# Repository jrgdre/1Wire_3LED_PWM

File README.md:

# 1Wire_3LED_PWM
How to drive 3 LEDs with 1 wire using Texas Intrument's TLC59731 PWM chip.

Find the in depth documentation at http://www.drechsler-it.de/Electronics_1Wire3LedPWM_TLC59731.html

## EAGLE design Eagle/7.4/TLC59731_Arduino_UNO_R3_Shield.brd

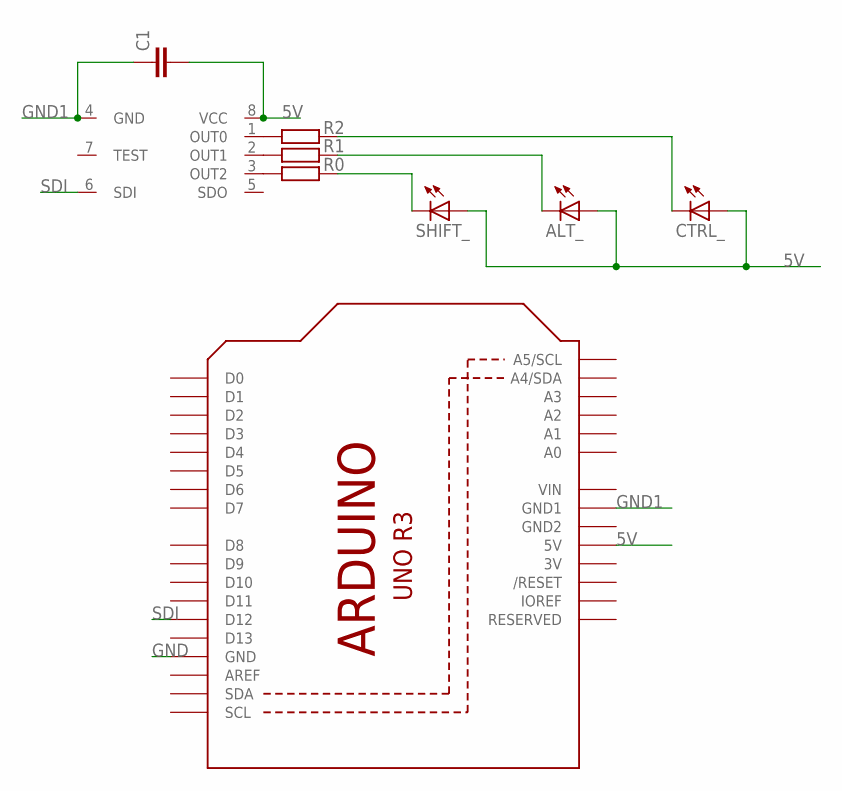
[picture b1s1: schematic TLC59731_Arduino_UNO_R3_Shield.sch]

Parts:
ALT_: LEDSMT1206; 1206
C1: CC0402; C0402
CTRL_: LEDSMT1206; 1206
M2: ARDUINO_UNO_R3_EXT
R0, R1, R2: R_0402; R0402
SHIFT_: LEDSMT1206; 1206
U1: TLC59731; SOIC8_208MIL

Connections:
3V: M2.3V
5V: ALT_.A, C1.2, CTRL_.A, M2.5V, SHIFT_.A, U1.8 (VCC)
GND: M2.GND
GND1: C1.1, M2.GND1, U1.4 (GND)
GND2: M2.GND2
unnamed: R0.2, U1.3 (OUT2)
unnamed: R1.2, U1.2 (OUT1)
unnamed: R2.2, U1.1 (OUT0)
unnamed: R0.1, SHIFT_.C
unnamed: ALT_.C, R1.1
unnamed: CTRL_.C, R2.1
SDI: M2.D12, U1.6 (SDI)
VIN: M2.VIN

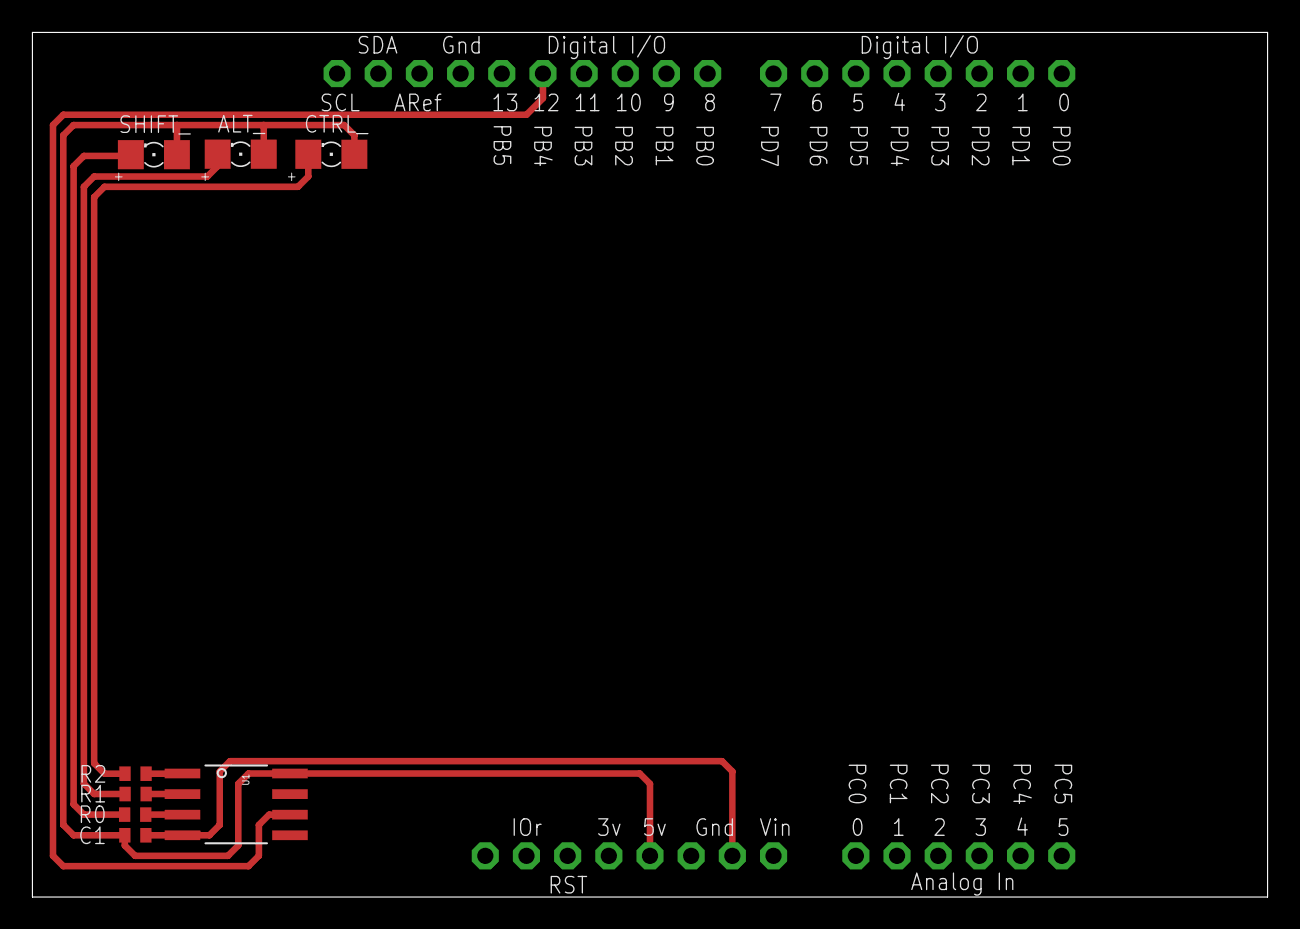
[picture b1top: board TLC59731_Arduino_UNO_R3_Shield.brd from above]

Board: 2 copper layers, 76.2 x 53.3 mm, 9 parts (0 on the bottom side), 9 nets.

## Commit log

2016-05-07 added Cypress CY8C4247LQI-BL483 PSoC_Creator3 HelloTLC59731 project
2016-05-07 added README.md and LICENSE.md
2016-05-07 added Eagle 7.4 layout
2016-05-08 updated Documentation
2016-05-10 added Arduino Uno R3 project
2016-05-10 fixed Arduino UUNO pathname
2016-05-10 added Atmel 328PB_Xplained Studio7 project
